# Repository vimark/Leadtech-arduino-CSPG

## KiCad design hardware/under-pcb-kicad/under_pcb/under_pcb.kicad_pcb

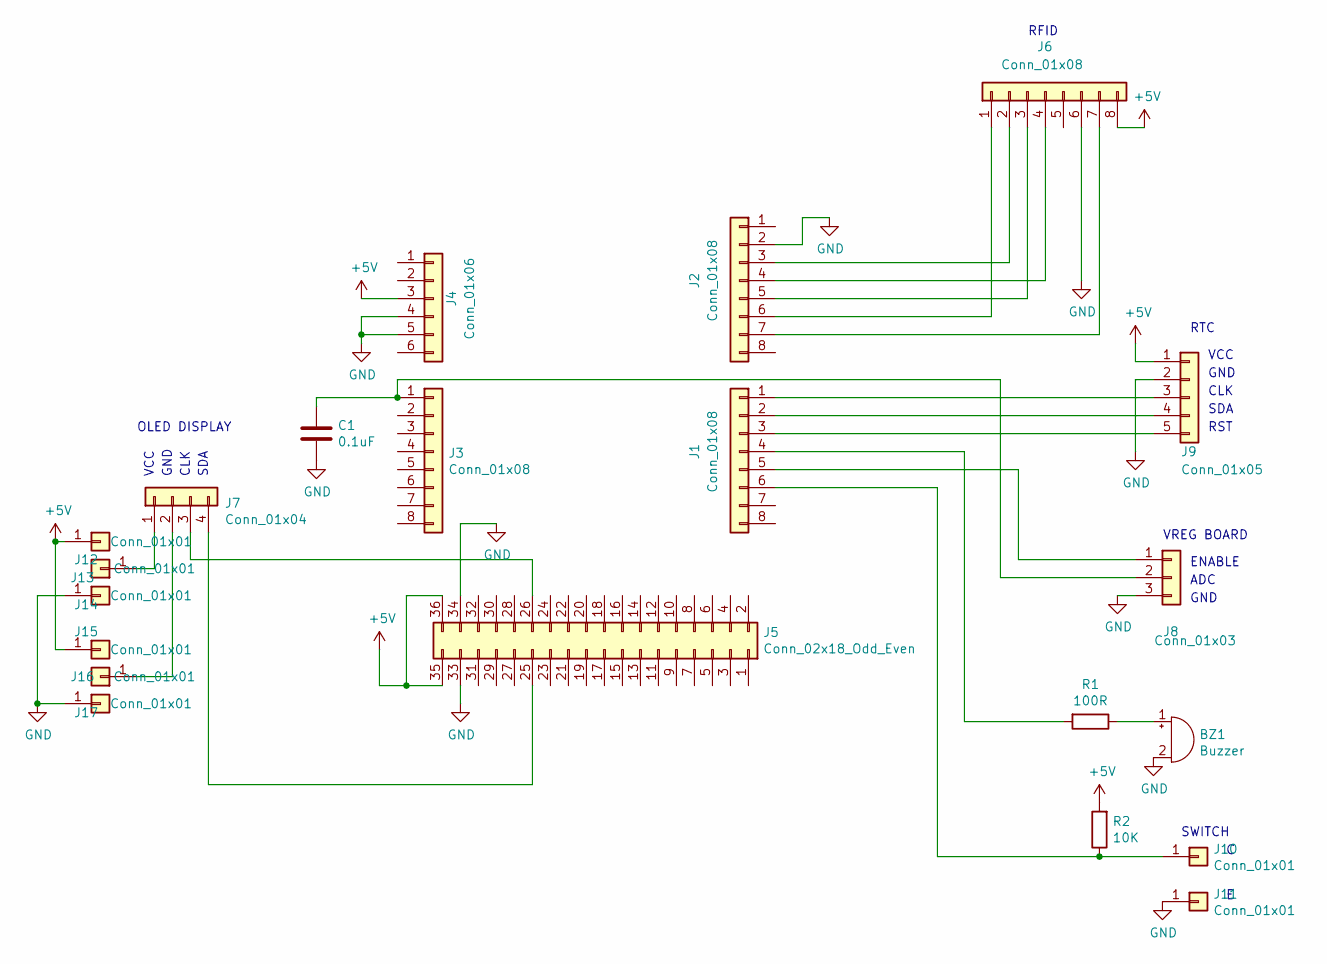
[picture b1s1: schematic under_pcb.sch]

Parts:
BZ1: Buzzer; Buzzer_12x9.5RM7.6
C1: 0.1uF; C_Disc_D5.0mm_W2.5mm_P2.50mm
J1, J2, J3, J6: Conn_01x08; PinSocket_1x08_P2.54mm_Vertical
J4: Conn_01x06; PinSocket_1x06_P2.54mm_Vertical
J5: Conn_02x18_Odd_Even; PinSocket_2x18_P2.54mm_Vertical
J7: Conn_01x04; PinSocket_1x04_P2.54mm_Vertical
J8: Conn_01x03; PinSocket_1x03_P2.54mm_Vertical
J9: Conn_01x05; PinSocket_1x05_P2.54mm_Vertical
J10, J11, J12, J13, J14, J15, J16, J17: Conn_01x01; PinSocket_1x01_P2.54mm_Vertical
R1: 100R; R_Axial_DIN0207_L6.3mm_D2.5mm_P10.16mm_Horizontal
R2: 10K; R_Axial_DIN0207_L6.3mm_D2.5mm_P10.16mm_Horizontal

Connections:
+5V: J4.3, J5.35, J5.36, J6.8, J9.1, J12.1, J15.1, R2.2
GND: BZ1.2 (+), C1.2, J2.2, J4.4, J4.5, J5.33, J5.34, J6.6, J8.3, J9.2, J11.1, J14.1, J17.1
unnamed: BZ1.1 (-), R1.1
unnamed: C1.1, J3.1, J8.2
unnamed: J1.1, J9.3
unnamed: J1.2, J9.4
unnamed: J1.3, J9.5
unnamed: J1.4, R1.2
unnamed: J1.5, J8.1
unnamed: J1.6, J10.1, R2.1
unnamed: J2.3, J6.2
unnamed: J2.4, J6.4
unnamed: J2.5, J6.3
unnamed: J2.6, J6.1
unnamed: J2.7, J6.7
unnamed: J5.25, J7.4
unnamed: J5.26, J7.3
unnamed: J7.1, J13.1
unnamed: J7.2, J16.1

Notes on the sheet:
ENABLE
ADC
GND
VREG BOARD
RFID
RTC
VCC
CLK
SDA
RST
OLED DISPLAY
SWITCH

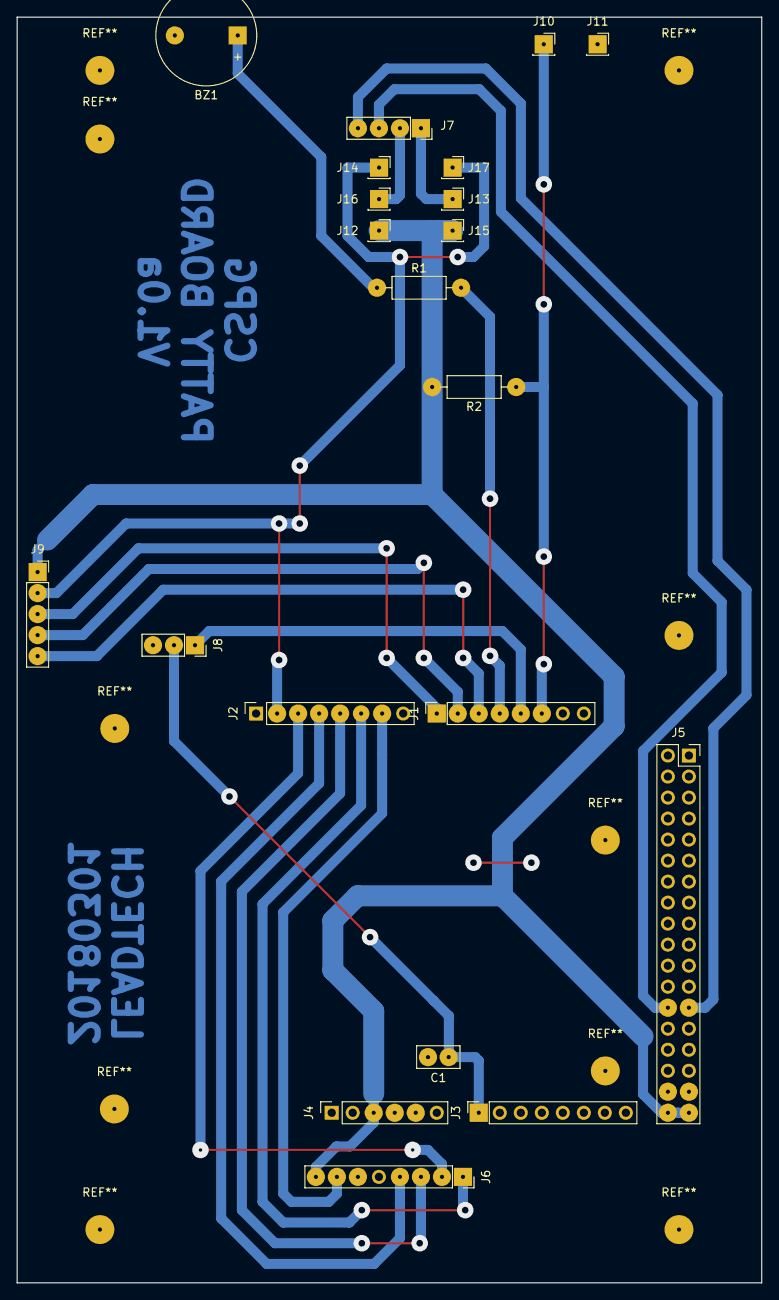
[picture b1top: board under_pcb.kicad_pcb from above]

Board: 2 copper layers, 90.0 x 153.0 mm, 21 parts (0 on the bottom side), 19 nets.

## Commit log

2019-07-27 add doucment sources
2019-08-09 add atmega1281 mcu
2019-08-23 add chip docs
2019-08-23 started routing schematic
2019-08-25 building schematic
2019-08-26 continue wiring schematic
2019-08-28 add project schedule excel, add RFID module on schematic
2019-08-30 continue wiring schematic, RFIF wiring done, level shifter done, add BOM with links on excel sheet
2019-08-30 continue on schematic work, add i2c OLED
2019-09-01 add box plate, i2c oled sketch
2019-09-04 applied changes from kim
2019-09-04 move files around, add readWrite for RFID read/write
2019-09-04 edited box plate drawing, added chip docs
2019-09-06 worked with enclosure design for demo set-up
2019-09-07 small update
2019-09-11 added buzzer function, add circuit for regulated output
2019-09-12 added resources docs
2019-09-13 made some rev on dwg and schematic
2019-09-14 update dwg
2019-09-15 added files
2019-09-16 add card UID writer sketch
2019-09-18 update files
2019-09-21 fix sizes of modules
2019-09-22 upload new references
2019-09-28 added spice sim
2019-09-28 add sketch for RTC
2019-09-28 update on some sketches
2019-10-02 temp note added
2019-10-02 add spice simulations, documents
2019-10-03 fix mounting holes for solar home kit
2019-10-06 small updates
2019-10-07 updated vendor box drawings
2019-10-07 fix cspg vendor sketch
2019-10-07 updates on vendo box
2019-10-08 fix vendor box
2019-10-08 add corel v14 of vendor box laser cutout
2019-10-10 move to do notes to other git repo, fix vendo box design
2019-10-12 add gizduino pins on schematic, add bug comment on value of month on vendor firmware, add time sketches
2019-10-15 fix bug when month is set to greater than 9, add PDF printout of schematic
2019-10-17 fix year display on standby, double the size of load text on printed reciept
2019-10-18 added costing and consting printouts
2019-10-27 made board for LM723, update prepaid metering module placement
2019-10-30 fix circuit and made 2 panelized board
2020-01-01 added new LM723 reference schematic from a known PSU
2020-01-09 varous files updates
2020-01-11 added test result excel
2020-01-31 renamed some docs
2020-02-04 fix grace period when overloaded
2020-02-08 revised prepaid metering front panel text
2020-02-09 added new identification functionality of RFID for each meter, fix time sync via monitor command
2020-02-10 implement card association to its meter, simple command line implementation via serial, configuration saving to RTC ram
2020-02-10 implement serial commands, fix RTC RAM settings partitioning on time out and time rate
2020-02-11 add more serial commands, add eeprom saving
2020-02-12 fix active status bug
2020-02-13 fix buzzer endifs, RTC now works
2020-02-17 added load deletion on vendor firmware, fix current not sensing when card was swiped on client firmware, added censor directives on client firmware
2020-02-18 add kicad under pcb
2020-02-19 wiring and routing under pcb
2020-02-19 board routing donr on under_pcb/patty board
2020-02-20 update results, updated patty board
2020-02-21 edit CSPG arduino hardware
2020-02-22 test result updated for electronic load reading, changed meter user to master user for testing only
2020-02-25 worked on schematic
2020-02-26 separated released firmware folder
2020-02-28 fix serial commands RATE, TIMOUT, working on ID command, add notes on tl494 schematic
2020-03-01 add supply jumper on OLED for patty board
2020-03-01 add power source manager op-amp wiring
2020-03-09 continue routing board
2020-03-09 routing
2020-03-17 done routing, add bom
2020-03-17 making bom
2020-03-18 finish routing main board and bom
2020-03-18 revision on main board
